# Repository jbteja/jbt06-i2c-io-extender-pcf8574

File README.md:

# I2C IO-expander for switching solenoid valves

> Image of the board:

> Limitations:
- On power-up, all the pins are active high till initialized.

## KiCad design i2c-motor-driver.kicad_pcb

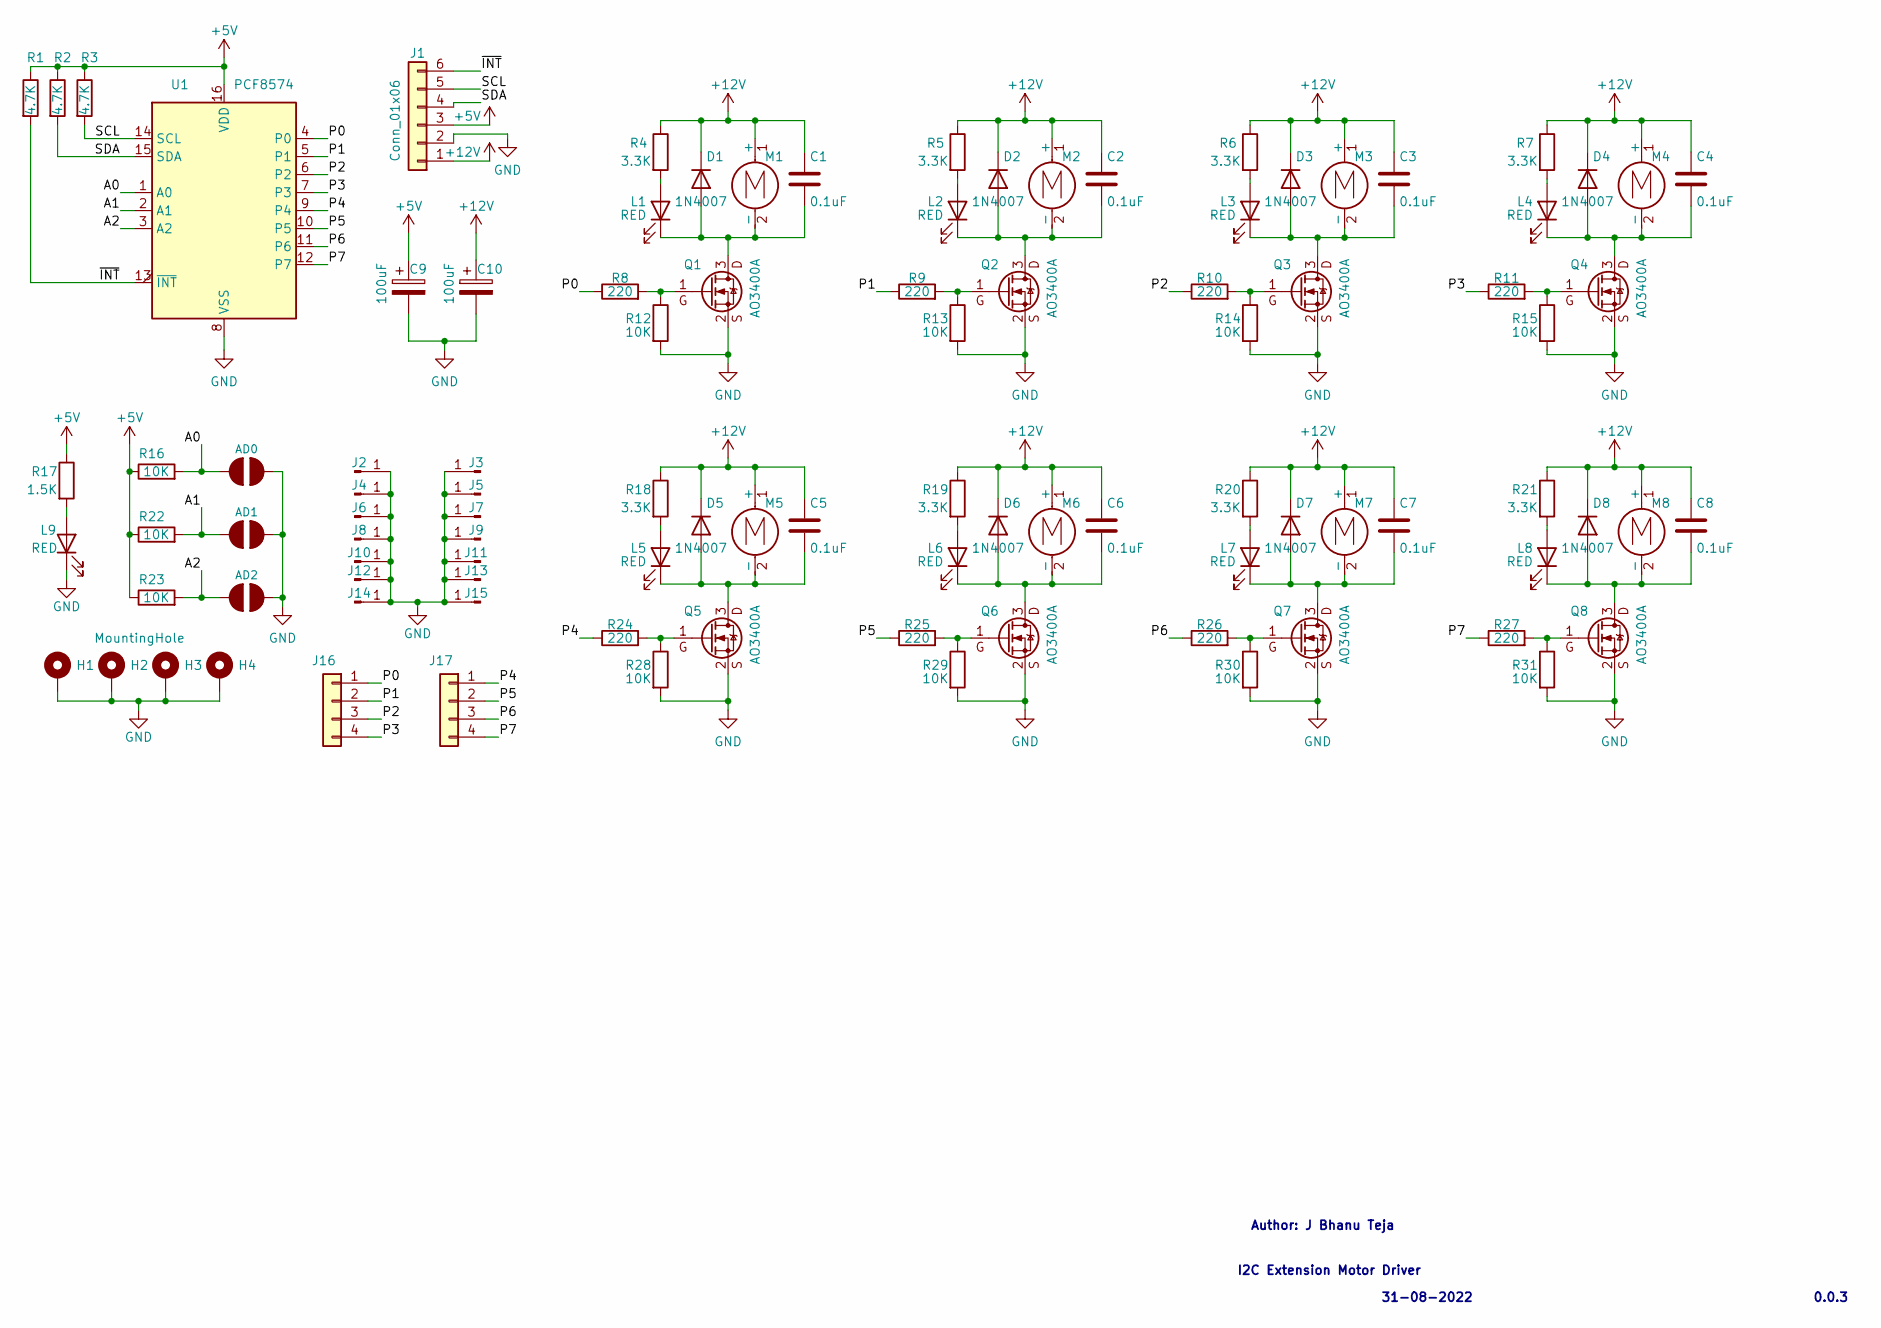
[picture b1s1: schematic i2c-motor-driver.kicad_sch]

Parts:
AD0, AD1, AD2: JUMPER-SMT_2_NO; SolderJumper-2_P1.3mm_Open_RoundedPad1.0x1.5mm
C1, C2, C3, C4, C5, C6, C7, C8: 0.1uF; C_0805_2012Metric
C9, C10: 100uF; CP_Elec_6.3x7.7
D1, D2, D3, D4, D5, D6, D7, D8: 1N4007; D_SMA
H1, H2, H3, H4: MountingHole; MountingHole_3.2mm_M3_Pad
J1: Conn_01x06; JST_EH_S6B-EH_1x06_P2.50mm_Horizontal
J2, J3, J4, J5, J6, J7, J8, J9, J10, J11, J12, J13, J14, J15: Conn_01x01_Male; 1X01
J16, J17: Conn_01x04; PinHeader_1x04_P2.54mm_Vertical
L1, L2, L3, L4, L5, L6, L7, L8, L9: RED; LED_0805_2012Metric
M1, M2, M3, M4, M5, M6, M7, M8: Motor_DC; JST_EH_S2B-EH_1x02_P2.50mm_Horizontal
Q1, Q2, Q3, Q4, Q5, Q6, Q7, Q8: AO3400A; SOT-23
R1, R2, R3: 4.7K; R_0805_2012Metric
R4, R5, R6, R7, R18, R19, R20, R21: 3.3K; R_0805_2012Metric
R8, R9, R10, R11, R24, R25, R26, R27: 220; R_0805_2012Metric
R12, R13, R14, R15, R16, R22, R23, R28, R29, R30, R31: 10K; R_0805_2012Metric
R17: 1.5K; R_0805_2012Metric
U1: PCF8574; SOIC-16W_7.5x10.3mm_P1.27mm

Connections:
+5V: C9.1, J1.3, R1.1, R2.1, R3.1, R16.1, R17.1, R22.1, R23.1, U1.16 (VDD)
+12V: C1.1, C2.1, C3.1, C4.1, C5.1, C6.1, C7.1, C8.1, C10.1, D1.1 (K), D2.1 (K), D3.1 (K), D4.1 (K), D5.1 (K), D6.1 (K), D7.1 (K), D8.1 (K), J1.1, M1.1 (+), M2.1 (+), M3.1 (+), M4.1 (+), M5.1 (+), M6.1 (+), M7.1 (+), M8.1 (+), R4.1, R5.1, R6.1, R7.1, R18.1, R19.1, R20.1, R21.1
/A0: AD0.1, R16.2, U1.1 (A0)
/A1: AD1.1, R22.2, U1.2 (A1)
/A2: AD2.1, R23.2, U1.3 (A2)
/P0: J16.1, R8.1, U1.4 (P0)
/P1: J16.2, R9.1, U1.5 (P1)
/P2: J16.3, R10.1, U1.6 (P2)
/P3: J16.4, R11.1, U1.7 (P3)
/P4: J17.1, R24.1, U1.9 (P4)
/P5: J17.2, R25.1, U1.10 (P5)
/P6: J17.3, R26.1, U1.11 (P6)
/P7: J17.4, R27.1, U1.12 (P7)
/SCL: J1.5, R3.2, U1.14 (SCL)
/SDA: J1.4, R2.2, U1.15 (SDA)
/~INT: J1.6, R1.2, U1.13 (~INT)
GND: AD0.2, AD1.2, AD2.2, C9.2, C10.2, H1.1, H2.1, H3.1, H4.1, J1.2, J2.1, J3.1, J4.1, J5.1, J6.1, J7.1, J8.1, J9.1, J10.1, J11.1, J12.1, J13.1, J14.1, J15.1, L9.1 (K), Q1.2 (S), Q2.2 (S), Q3.2 (S), Q4.2 (S), Q5.2 (S), Q6.2 (S), Q7.2 (S), Q8.2 (S), R12.2, R13.2, R14.2, R15.2, R28.2, R29.2, R30.2, R31.2, U1.8 (VSS)
unnamed: C1.2, D1.2 (A), L1.1 (K), M1.2 (-), Q1.3 (D)
unnamed: C2.2, D2.2 (A), L2.1 (K), M2.2 (-), Q2.3 (D)
unnamed: C3.2, D3.2 (A), L3.1 (K), M3.2 (-), Q3.3 (D)
unnamed: C4.2, D4.2 (A), L4.1 (K), M4.2 (-), Q4.3 (D)
unnamed: C5.2, D5.2 (A), L5.1 (K), M5.2 (-), Q5.3 (D)
unnamed: C6.2, D6.2 (A), L6.1 (K), M6.2 (-), Q6.3 (D)
unnamed: C7.2, D7.2 (A), L7.1 (K), M7.2 (-), Q7.3 (D)
unnamed: C8.2, D8.2 (A), L8.1 (K), M8.2 (-), Q8.3 (D)
unnamed: L1.2 (A), R4.2
unnamed: L2.2 (A), R5.2
unnamed: L3.2 (A), R6.2
unnamed: L4.2 (A), R7.2
unnamed: L5.2 (A), R18.2
unnamed: L6.2 (A), R19.2
unnamed: L7.2 (A), R20.2
unnamed: L8.2 (A), R21.2
unnamed: L9.2 (A), R17.2
unnamed: Q1.1 (G), R8.2, R12.1
unnamed: Q2.1 (G), R9.2, R13.1
unnamed: Q3.1 (G), R10.2, R14.1
unnamed: Q4.1 (G), R11.2, R15.1
unnamed: Q5.1 (G), R24.2, R28.1
unnamed: Q6.1 (G), R25.2, R29.1
unnamed: Q7.1 (G), R26.2, R30.1
unnamed: Q8.1 (G), R27.2, R31.1

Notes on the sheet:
0.0.3
Author: J Bhanu Teja
I2C Extension Motor Driver
31-08-2022

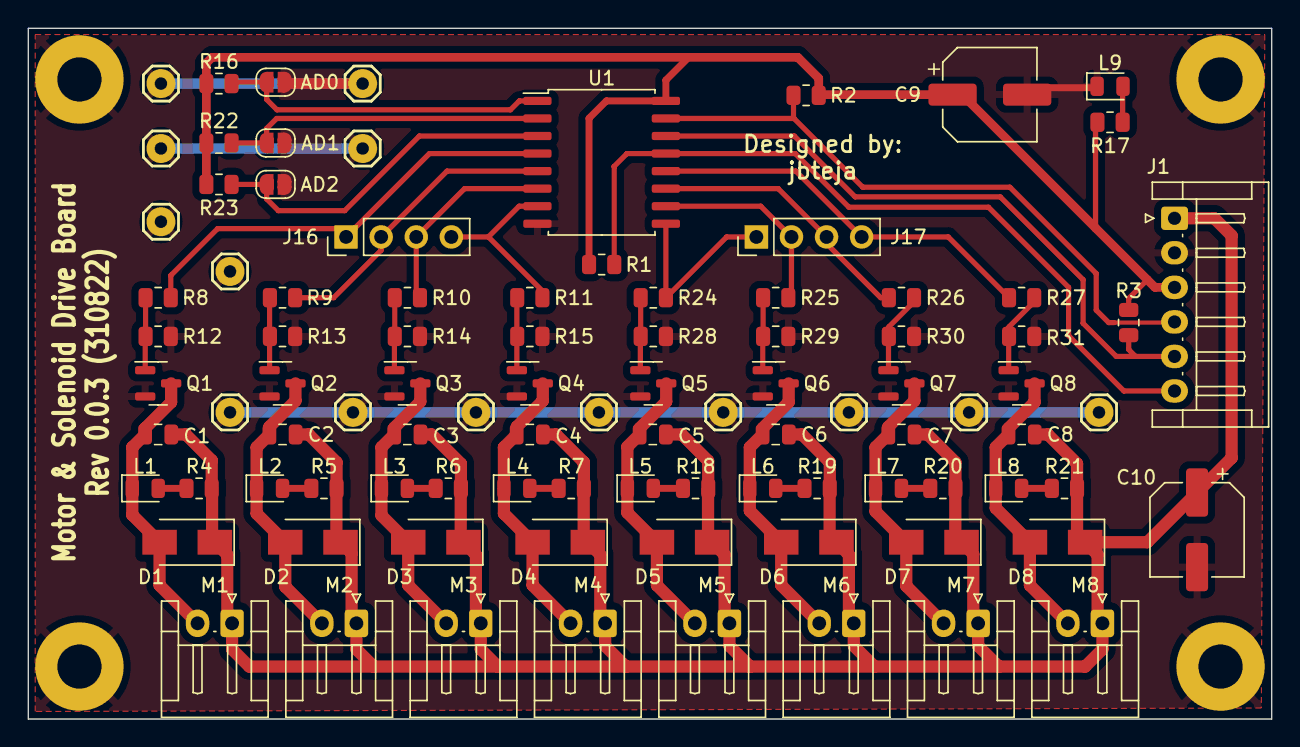
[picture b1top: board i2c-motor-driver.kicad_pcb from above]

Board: 2 copper layers, 90.0 x 50.0 mm, 99 parts (0 on the bottom side), 42 nets.

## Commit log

2023-06-21 Initial commit, Pushing all the staged changes
